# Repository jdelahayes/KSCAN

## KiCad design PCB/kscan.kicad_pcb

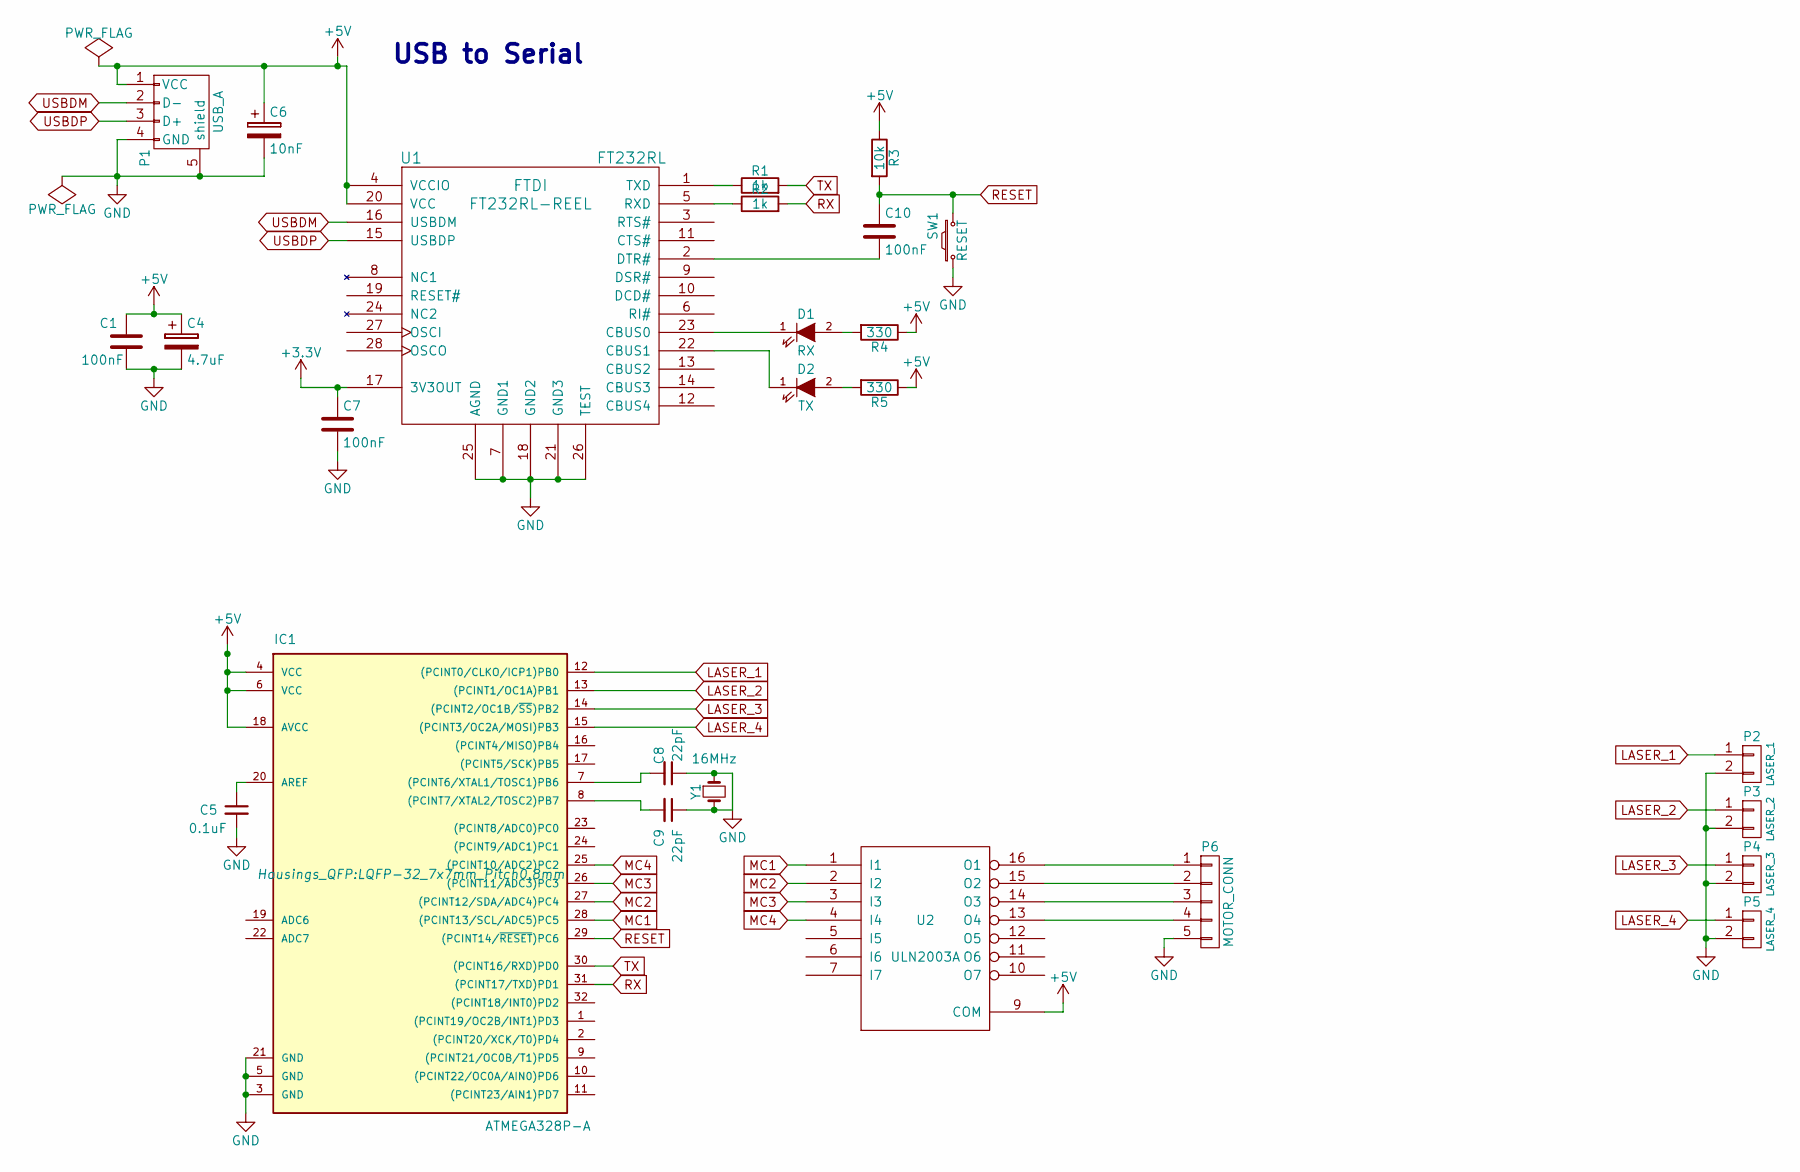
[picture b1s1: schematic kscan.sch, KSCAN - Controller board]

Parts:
C1, C7, C10: 100nF; C_0805
C4: 4.7uF; C_0805
C5: 0.1uF; C_0805
C6: 10nF; C_0805
C8, C9: 22pF; C_0805
D1: RX; LED_0805
D2: TX; LED_0805
IC1: ATMEGA328P-A; LQFP-32_7x7mm_Pitch0.8mm
P1: USB_A
P2: LASER_1; JST_XH_B02B-XH-A_02x2.50mm_Straight
P3: LASER_2; JST_XH_B02B-XH-A_02x2.50mm_Straight
P4: LASER_3; JST_XH_B02B-XH-A_02x2.50mm_Straight
P5: LASER_4; JST_XH_B02B-XH-A_02x2.50mm_Straight
P6: MOTOR_CONN; JST_XH_B05B-XH-A_05x2.50mm_Straight
R1, R2: 1k; R_0805
R3: 10k; R_0805
R4, R5: 330; R_0805
SW1: RESET; SW_SPST_B3S-1000
U1: FT232RL; SSOP-28_5.3x10.2mm_Pitch0.65mm; MPN FT232RL-REEL
U2: ULN2003A; SOIC-16_3.9x9.9mm_Pitch1.27mm
Y1: 16MHz; Crystal_SMD_HC49-SD

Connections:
+3V3: C7.1, U1.17 (3V3OUT)
+5V: C1.1, C4.1, C6.1, IC1.4 (VCC), IC1.6 (VCC), IC1.18 (AVCC), P1.1 (VCC), R3.1, R4.1, R5.1, U1.4 (VCCIO), U1.20 (VCC), U2.9 (COM)
GND: C1.2, C4.2, C5.2, C6.2, C7.2, C8.1, C9.1, IC1.3 (GND), IC1.5 (GND), IC1.21 (GND), P1.4 (GND), P1.5 (shield), P2.2, P3.2, P4.2, P5.2, P6.5, SW1.1, U1.7 (GND1), U1.18 (GND2), U1.21 (GND3), U1.25 (AGND), U1.26 (TEST), U2.8 (GND), Y1.1, Y1.2
LASER_1: IC1.12 ((PCINT0/CLKO/ICP1)PB0), P2.1
LASER_2: IC1.13 ((PCINT1/OC1A)PB1), P3.1
LASER_3: IC1.14 ((PCINT2/OC1B/~SS~)PB2), P4.1
LASER_4: IC1.15 ((PCINT3/OC2A/MOSI)PB3), P5.1
MC1: IC1.28 ((PCINT13/SCL/ADC5)PC5), U2.1 (I1)
MC2: IC1.27 ((PCINT12/SDA/ADC4)PC4), U2.2 (I2)
MC3: IC1.26 ((PCINT11/ADC3)PC3), U2.3 (I3)
MC4: IC1.25 ((PCINT10/ADC2)PC2), U2.4 (I4)
unnamed: C5.1, IC1.20 (AREF)
unnamed: C8.2, IC1.7 ((PCINT6/XTAL1/TOSC1)PB6)
unnamed: C9.2, IC1.8 ((PCINT7/XTAL2/TOSC2)PB7)
unnamed: C10.2, U1.2 (DTR#)
unnamed: D1.1 (K), U1.23 (CBUS0)
unnamed: D1.2 (A), R4.2
unnamed: D2.1 (K), U1.22 (CBUS1)
unnamed: D2.2 (A), R5.2
unnamed: P6.1, U2.16 (O1)
unnamed: P6.2, U2.15 (O2)
unnamed: P6.3, U2.14 (O3)
unnamed: P6.4, U2.13 (O4)
unnamed: R1.1, U1.1 (TXD)
unnamed: R2.1, U1.5 (RXD)
RESET: C10.1, IC1.29 ((PCINT14/~RESET~)PC6), R3.2, SW1.2
RX: IC1.31 ((PCINT17/TXD)PD1), R2.2
TX: IC1.30 ((PCINT16/RXD)PD0), R1.2
USBDM: P1.2 (D-), U1.16 (USBDM)
USBDP: P1.3 (D+), U1.15 (USBDP)

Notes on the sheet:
USB to Serial

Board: 2 copper layers, 26 parts (0 on the bottom side), 30 nets, no tracks yet.

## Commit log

2017-03-12 Add a README.md
2017-03-12 Adding netlist
2017-03-21 Change pin mapping
